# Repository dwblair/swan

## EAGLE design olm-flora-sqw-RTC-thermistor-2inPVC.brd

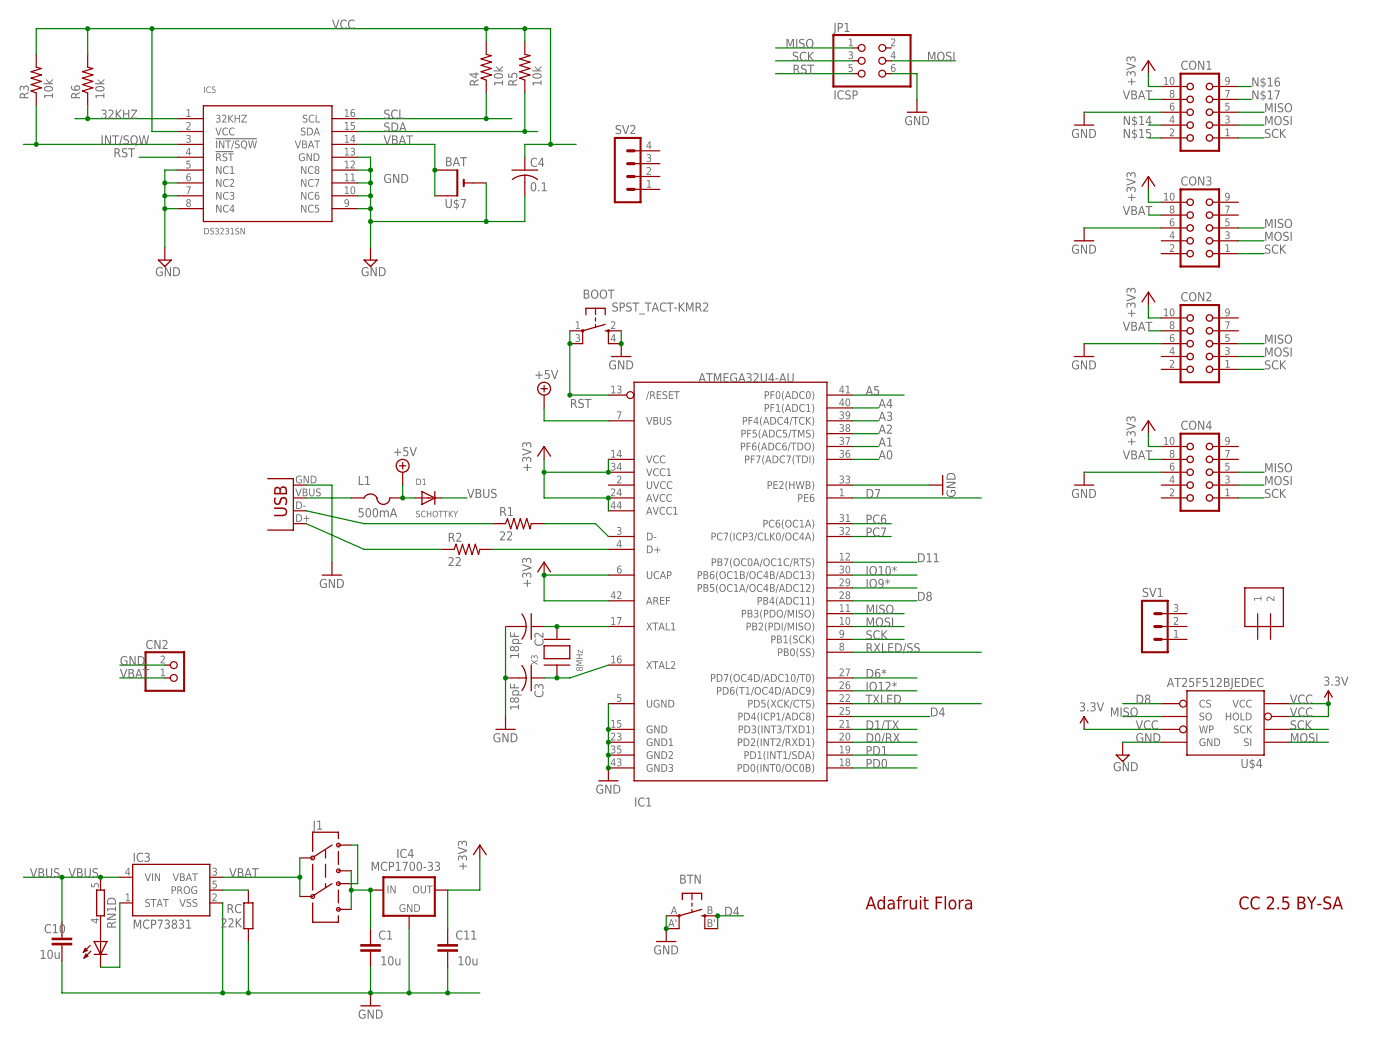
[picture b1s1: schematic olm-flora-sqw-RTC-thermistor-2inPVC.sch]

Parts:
BOOT: SPST_TACT-KMR2; KMR2
BTN: EVQQ2; EVQ-Q2
C1, C10, C11: 10u; C0805
C2, C3: 18pF; C0805K
C4: 0.1; C0805K
CHG: 0805; CHIPLED_0805
CN2: JST_2PIN-SMT-RA; JST-PH-2-SMT-RA
CON1, CON2, CON3, CON4: CON10
D1: SCHOTTKY; SOD-123
IC1: ATMEGA32U4-AU; TQFP44
IC3: MCP73831; SOT23-5
IC4: MCP1700-33; SOT23
IC5: DS3231SN; SO16W
J1: AYZ0202
J2: 1X2-3.5MM
JP1: ICSP; 2X03
L1: 500mA; R1206
R1, R2: 22; R0805
R3, R4, R5, R6: 10k; R0805
RC: 22K; R0805
RN1: 4R-NEXB38V; EXB38V
SV1: MA03-1
SV2: MA04-1
U$4: AT25F512BJEDEC; SO08
U$7: BAT; CR1220-SMD
X1: USBSMD; USB-MINIB
X3: 8MHz; NX5032

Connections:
32KHZ: IC5.1 (32KHZ), R6.1
+3V3: C11.1, CON1.10, CON2.10, CON3.10, CON4.10, IC1.6 (UCAP), IC1.14 (VCC), IC1.24 (AVCC), IC1.34 (VCC1), IC1.42 (AREF), IC1.44 (AVCC1), IC4.2 (OUT)
+5V: D1.A, IC1.7 (VBUS), L1.2
A0: IC1.36 (PF7(ADC7(TDI))
A1: IC1.37 (PF6(ADC6/TDO))
A2: IC1.38 (PF5(ADC5/TMS))
A3: IC1.39 (PF4(ADC4/TCK))
A4: IC1.40 (PF1(ADC1))
A5: IC1.41 (PF0(ADC0))
D0/RX: IC1.20 (PD2(INT2/RXD1))
D1/TX: IC1.21 (PD3(INT3/TXD1))
D4: BTN.B (S), BTN.B' (S1), IC1.25 (PD4(ICP1/ADC8))
D6*: IC1.27 (PD7(OC4D/ADC10/T0))
D7: IC1.1 (PE6)
D8: IC1.28 (PB4(ADC11)), U$4.1_CS (CS)
D11: IC1.12 (PB7(OC0A/OC1C/RTS))
GND: BOOT.2 (S), BOOT.4 (S1), BTN.A, BTN.A' (P1), C1.2, C2.2, C3.2, C4.2, C10.2, C11.2, CN2.2 (1), CON1.6, CON2.6, CON3.6, CON4.6, IC1.5 (UGND), IC1.15 (GND), IC1.23 (GND1), IC1.33 (PE2(HWB)), IC1.35 (GND2), IC1.43 (GND3), IC3.2 (VSS), IC4.1 (GND), IC5.5 (NC1), IC5.6 (NC2), IC5.7 (NC3), IC5.8 (NC4), IC5.9 (NC5), IC5.10 (NC6), IC5.11 (NC7), IC5.12 (NC8), IC5.13 (GND), JP1.6, RC.1, U$4.4_GND (GND), U$7.-, X1.GND
INT/SQW: IC5.3 (!INT/SQW), R3.1
IO9*: IC1.29 (PB5(OC1A/OC4B/ADC12))
IO10*: IC1.30 (PB6(OC1B/OC4B/ADC13))
IO12*: IC1.26 (PD6(T1/OC4D/ADC9))
MISO: CON1.5, CON2.5, CON3.5, CON4.5, IC1.11 (PB3(PDO/MISO)), JP1.1, U$4.2_SO (SO)
MOSI: CON1.3, CON2.3, CON3.3, CON4.3, IC1.10 (PB2(PDI/MISO)), JP1.4, U$4.5_SI (SI)
unnamed: CHG.C, IC3.1 (STAT)
unnamed: R2.1, X1.D+
unnamed: IC1.3 (D-), R1.2
unnamed: IC1.4 (D+), R2.2
unnamed: R1.1, X1.D-
unnamed: C2.1, IC1.17 (XTAL1), X3.P$2
unnamed: C3.1, IC1.16 (XTAL2), X3.P$1
unnamed: IC3.5 (PROG), RC.2
unnamed: J1.3 (1), J1.6 (4)
unnamed: CHG.A, RN1.4 (1)
PC6: IC1.31 (PC6(OC1A))
PC7: IC1.32 (PC7(ICP3/CLK0/OC4A))
PD0: IC1.18 (PD0(INT0/OC0B))
PD1: IC1.19 (PD1(INT1/SDA))
RST: BOOT.1, BOOT.3 (P1), IC1.13 (/RESET), IC5.4 (!RST), JP1.5
RXLED/SS: IC1.8 (PB0(SS))
SCK: CON1.1, CON2.1, CON3.1, CON4.1, IC1.9 (PB1(SCK)), JP1.3, U$4.6_SCK (SCK)
SCL: IC5.16 (SCL), R4.1
SDA: IC5.15 (SDA), R5.1
TXLED: IC1.22 (PD5(XCK/CTS))
VBAT: CN2.1 (2), CON1.8, CON2.8, CON3.8, CON4.8, IC3.3 (VBAT), IC5.14 (VBAT), J1.2, J1.5, U$7.+$1 (+), U$7.+$2 (+1)
VBUS: C10.1, D1.C, IC3.4 (VIN), L1.1, RN1.5 (2), X1.VBUS
VCC: C4.1, IC5.2 (VCC), R3.2, R4.2, R5.2, R6.2, U$4.3_WP (WP), U$4.7_HOLD (HOLD), U$4.8_VCC (VCC)
VDD: C1.1, IC4.3 (IN), J1.1 (3), J1.4 (6)

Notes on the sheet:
Adafruit Flora
CC 2.5 BY-SA

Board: 2 copper layers, 37 parts (1 on the bottom side), 27 nets, no tracks yet.

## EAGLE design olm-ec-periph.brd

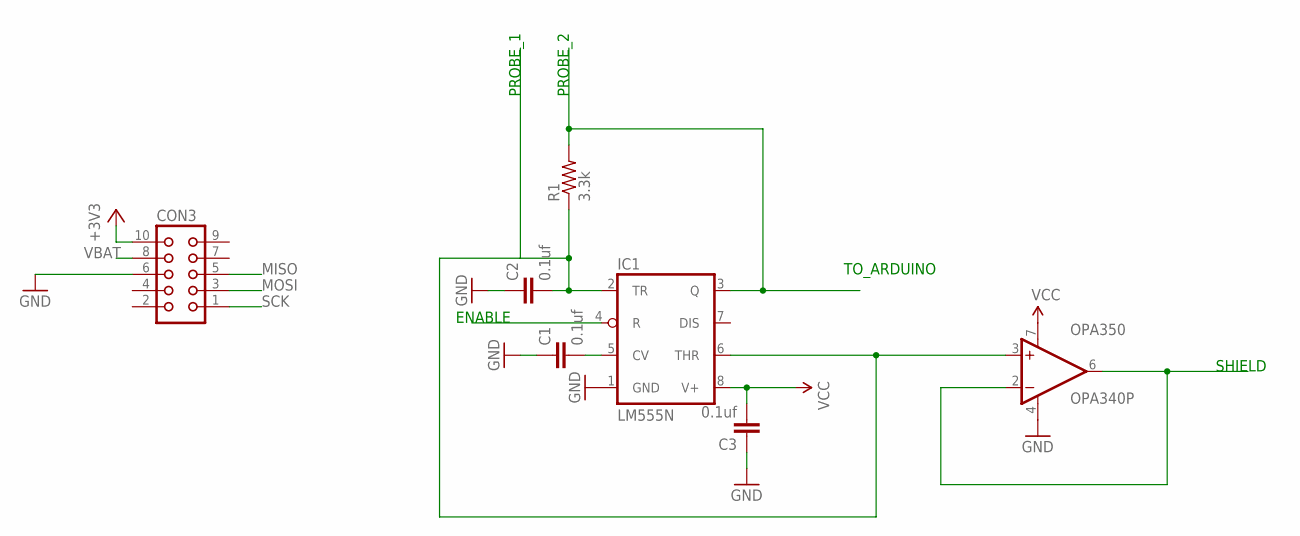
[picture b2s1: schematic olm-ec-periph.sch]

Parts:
C1, C2, C3: 0.1uf; C025-025X050
CON3: CON10
IC1: LM555N; DIL08
OPA350: OPA340P; DIL08
R1: 3.3k; 0207/10

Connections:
+3V3: CON3.10
ENABLE: IC1.4 (R)
GND: C1.1, C2.1, C3.1, CON3.6, IC1.1 (GND), OPA350.4 (V-)
MISO: CON3.5
MOSI: CON3.3
unnamed: C1.2, IC1.5 (CV)
PROBE_1: C2.2, IC1.2 (TR), IC1.6 (THR), OPA350.3 (+IN), R1.1
PROBE_2: IC1.3 (Q), R1.2
SCK: CON3.1
SHIELD: OPA350.2 (-IN), OPA350.6 (OUT)
VBAT: CON3.8
VCC: C3.2, IC1.8 (V+), OPA350.7 (V+)

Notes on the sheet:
PROBE_1
PROBE_2
SHIELD
ENABLE
TO_ARDUINO

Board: 2 copper layers, 7 parts (0 on the bottom side), 6 nets, no tracks yet.

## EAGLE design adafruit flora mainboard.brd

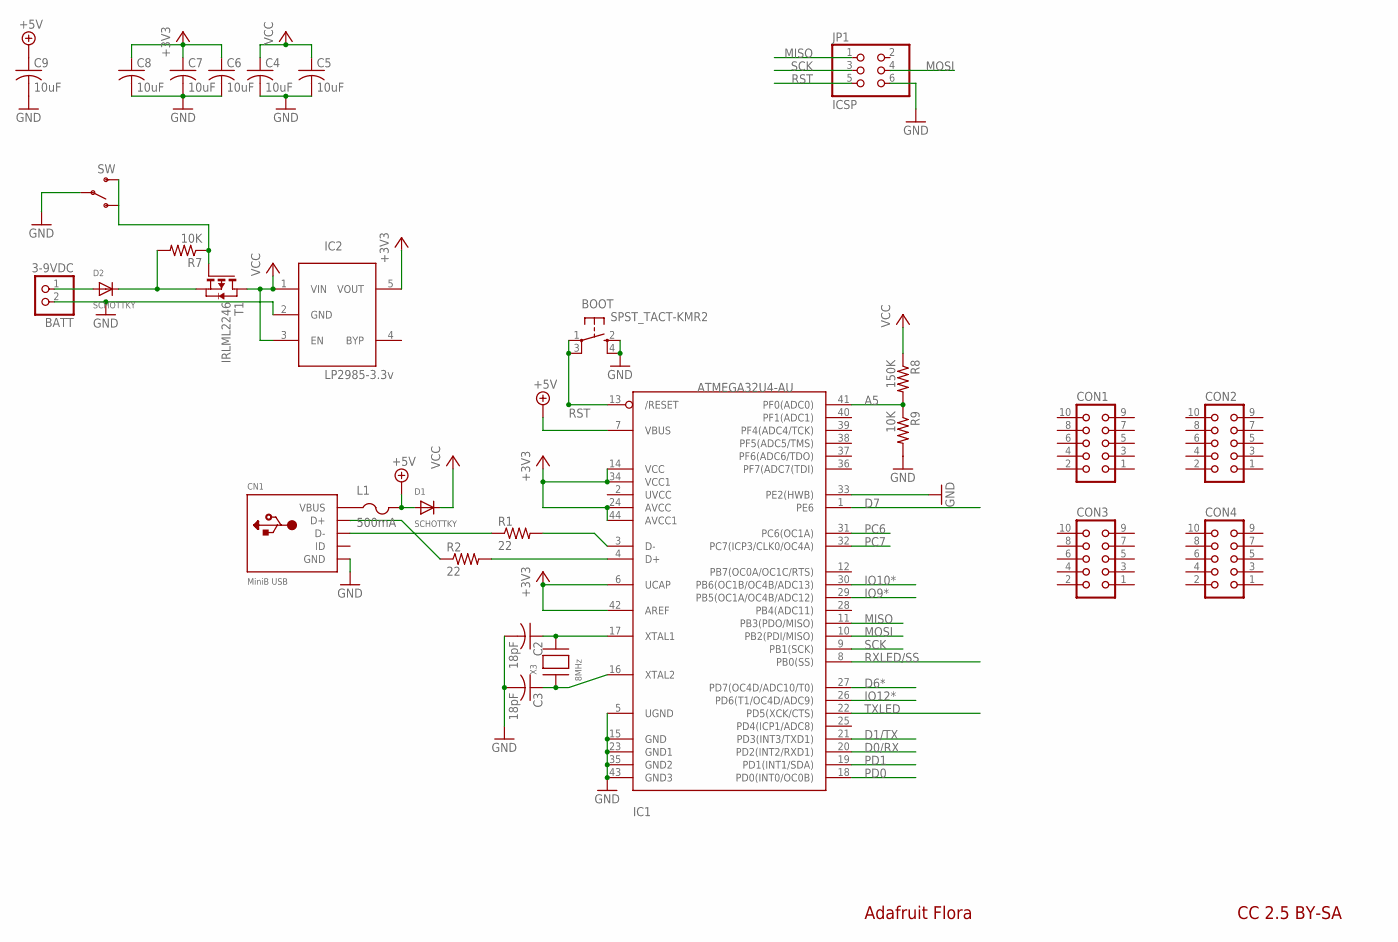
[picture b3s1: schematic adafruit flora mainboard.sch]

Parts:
BATT: 3-9VDC; JST-PH-2-SMT-RA
BOOT: SPST_TACT-KMR2; KMR2
C2, C3: 18pF; C0805K
C4, C5, C6, C7, C8, C9: 10uF; C0805K
CN1: MiniB USB; USB-MINIB_LARGER
CON1, CON2, CON3, CON4: CON10
D1, D2: SCHOTTKY; SOD-123
IC1: ATMEGA32U4-AU; TQFP44
IC2: LP2985-3.3v; SOT23-5L
JP1: ICSP; 2X03
L1: 500mA; R1206
R1, R2: 22; R0805
R7, R9: 10K; R0805
R8: 150K; R0805
SW: SPDT; SWITCH-SPDT-SMD
T1: IRLML2246; SOT-23
X3: 8MHz; NX5032

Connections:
+3V3: C6.1, C7.1, C8.1, IC1.6 (UCAP), IC1.14 (VCC), IC1.24 (AVCC), IC1.34 (VCC1), IC1.42 (AREF), IC1.44 (AVCC1), IC2.5 (VOUT)
+5V: C9.1, D1.A, IC1.7 (VBUS), L1.2
A5: IC1.41 (PF0(ADC0)), R8.2, R9.1
D0/RX: IC1.20 (PD2(INT2/RXD1))
D1/TX: IC1.21 (PD3(INT3/TXD1))
D6*: IC1.27 (PD7(OC4D/ADC10/T0))
D7: IC1.1 (PE6)
GND: BATT.2 (1), BOOT.2 (S), BOOT.4 (S1), C2.2, C3.2, C4.2, C5.2, C6.2, C7.2, C8.2, C9.2, CN1.GND, IC1.5 (UGND), IC1.15 (GND), IC1.23 (GND1), IC1.33 (PE2(HWB)), IC1.35 (GND2), IC1.43 (GND3), IC2.2 (GND), JP1.6, R9.2, SW.2
IO9*: IC1.29 (PB5(OC1A/OC4B/ADC12))
IO10*: IC1.30 (PB6(OC1B/OC4B/ADC13))
IO12*: IC1.26 (PD6(T1/OC4D/ADC9))
MISO: IC1.11 (PB3(PDO/MISO)), JP1.1
MOSI: IC1.10 (PB2(PDI/MISO)), JP1.4
unnamed: CN1.D+, R2.1
unnamed: IC1.3 (D-), R1.2
unnamed: IC1.4 (D+), R2.2
unnamed: CN1.D-, R1.1
unnamed: D2.C, R7.2, T1.2 (S)
unnamed: BATT.1 (2), D2.A
unnamed: C2.1, IC1.17 (XTAL1), X3.P$2
unnamed: C3.1, IC1.16 (XTAL2), X3.P$1
unnamed: R7.1, SW.3 (S), T1.3 (G)
PC6: IC1.31 (PC6(OC1A))
PC7: IC1.32 (PC7(ICP3/CLK0/OC4A))
PD0: IC1.18 (PD0(INT0/OC0B))
PD1: IC1.19 (PD1(INT1/SDA))
RST: BOOT.1, BOOT.3 (P1), IC1.13 (/RESET), JP1.5
RXLED/SS: IC1.8 (PB0(SS))
SCK: IC1.9 (PB1(SCK)), JP1.3
TXLED: IC1.22 (PD5(XCK/CTS))
VBUS: CN1.VBUS, L1.1
VCC: C4.1, C5.1, D1.C, IC2.1 (VIN), IC2.3 (EN), R8.1, T1.1 (D)

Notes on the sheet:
Adafruit Flora
CC 2.5 BY-SA

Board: 2 copper layers, 29 parts (0 on the bottom side), 19 nets, no tracks yet.

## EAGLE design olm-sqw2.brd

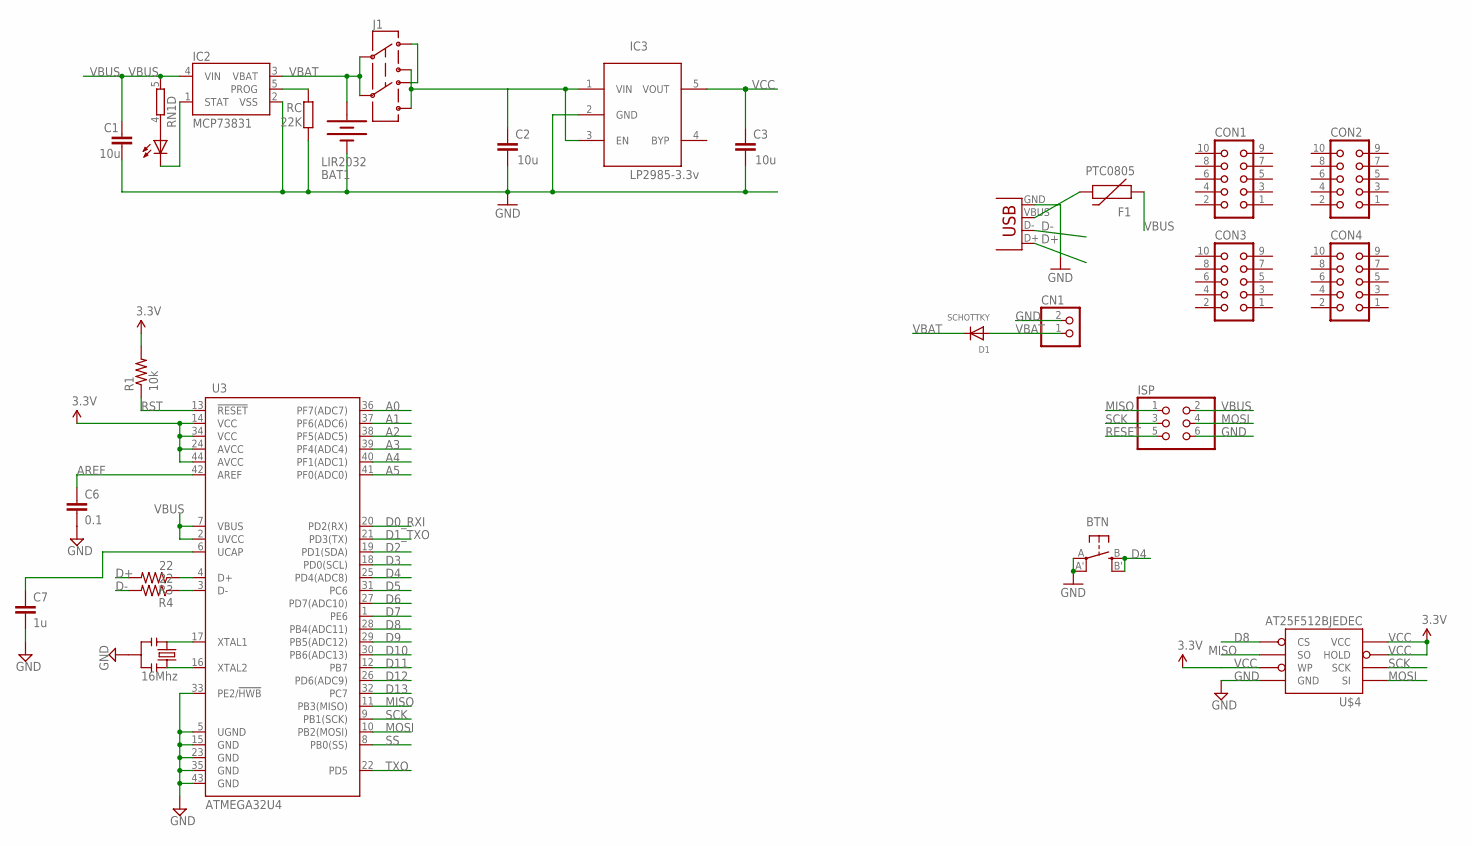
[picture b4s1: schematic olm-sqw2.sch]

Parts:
BAT1: LIR2032; BATTCOM_20MM_PTH_SMT
BTN: EVQQ2; EVQ-Q2
C1, C2, C3: 10u; C0805
C6: 0.1; 0603-CAP
C7: 1u; 0603-CAP
CHG: 0805; CHIPLED_0805
CN1: JST_2PIN-SMT-RA; JST-PH-2-SMT-RA
CON1, CON2, CON3, CON4: CON10
D1: SCHOTTKY; SOD-123
F1: PTC0805; 0805-PTC
IC2: MCP73831; SOT23-5
IC3: LP2985-3.3v; SOT23-5L
ISP: PINHD-2X3; 2X03
J1: AYZ0202
R1: 10k; 0603-RES
R3, R4: 22; 0603-RES
RC: 22K; R0805
RN1: 4R-NEXB38V; EXB38V
U3: ATMEGA32U4; QFN-44-NOPAD
U$4: AT25F512BJEDEC; SO08
X1: USBSMD; USB-MINIB
X2: 16Mhz; RESONATOR-SMD

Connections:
A0: U3.36 (PF7(ADC7))
A1: U3.37 (PF6(ADC6))
A2: U3.38 (PF5(ADC5))
A3: U3.39 (PF4(ADC4))
A4: U3.40 (PF1(ADC1))
A5: U3.41 (PF0(ADC0))
AREF: C6.1, U3.42 (AREF)
D0_RXI: U3.20 (PD2(RX))
D1_TXO: U3.21 (PD3(TX))
D2: U3.19 (PD1(SDA))
D3: U3.18 (PD0(SCL))
D4: BTN.B (S), BTN.B' (S1), U3.25 (PD4(ADC8))
D5: U3.31 (PC6)
D6: U3.27 (PD7(ADC10))
D7: U3.1 (PE6)
D8: U3.28 (PB4(ADC11)), U$4.1_CS (CS)
D9: U3.29 (PB5(ADC12))
D10: U3.30 (PB6(ADC13))
D11: U3.12 (PB7)
D12: U3.26 (PD6(ADC9))
D13: U3.32 (PC7)
D+: R3.2, X1.D+
D-: R4.2, X1.D-
GND: BAT1.P$1 (-), BTN.A, BTN.A' (P1), C1.2, C2.2, C3.2, C6.2, C7.2, CN1.2 (1), IC2.2 (VSS), IC3.2 (GND), ISP.6, RC.1, U3.5 (UGND), U3.15 (GND), U3.23 (GND), U3.33 (PE2/!HWB), U3.35 (GND), U3.43 (GND), U$4.4_GND (GND), X1.GND, X2.2
MISO: ISP.1, U3.11 (PB3(MISO)), U$4.2_SO (SO)
MOSI: ISP.4, U3.10 (PB2(MOSI)), U$4.5_SI (SI)
unnamed: J1.3 (1), J1.6 (4)
unnamed: U3.16 (XTAL2), X2.3
unnamed: CHG.C, IC2.1 (STAT)
unnamed: IC2.5 (PROG), RC.2
unnamed: U3.17 (XTAL1), X2.1
unnamed: C7.1, U3.6 (UCAP)
unnamed: R3.1, U3.4 (D+)
unnamed: CHG.A, RN1.4 (1)
unnamed: R4.1, U3.3 (D-)
RESET: ISP.5
RST: R1.1, U3.13 (!RESET)
SCK: ISP.3, U3.9 (PB1(SCK)), U$4.6_SCK (SCK)
SS: U3.8 (PB0(SS))
TXO: U3.22 (PD5)
VBAT: BAT1.P$2 (+), CN1.1 (2), D1.A, D1.C, IC2.3 (VBAT), J1.2, J1.5
VBUS: C1.1, F1.1, F1.2, IC2.4 (VIN), ISP.2, RN1.5 (2), U3.2 (UVCC), U3.7 (VBUS), X1.VBUS
VCC: C3.1, IC3.5 (VOUT), R1.2, U3.14 (VCC), U3.24 (AVCC), U3.34 (VCC), U3.44 (AVCC), U$4.3_WP (WP), U$4.7_HOLD (HOLD), U$4.8_VCC (VCC)
VDD: C2.1, IC3.1 (VIN), IC3.3 (EN), J1.1 (3), J1.4 (6)

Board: 2 copper layers, 28 parts (1 on the bottom side), 23 nets, no tracks yet.

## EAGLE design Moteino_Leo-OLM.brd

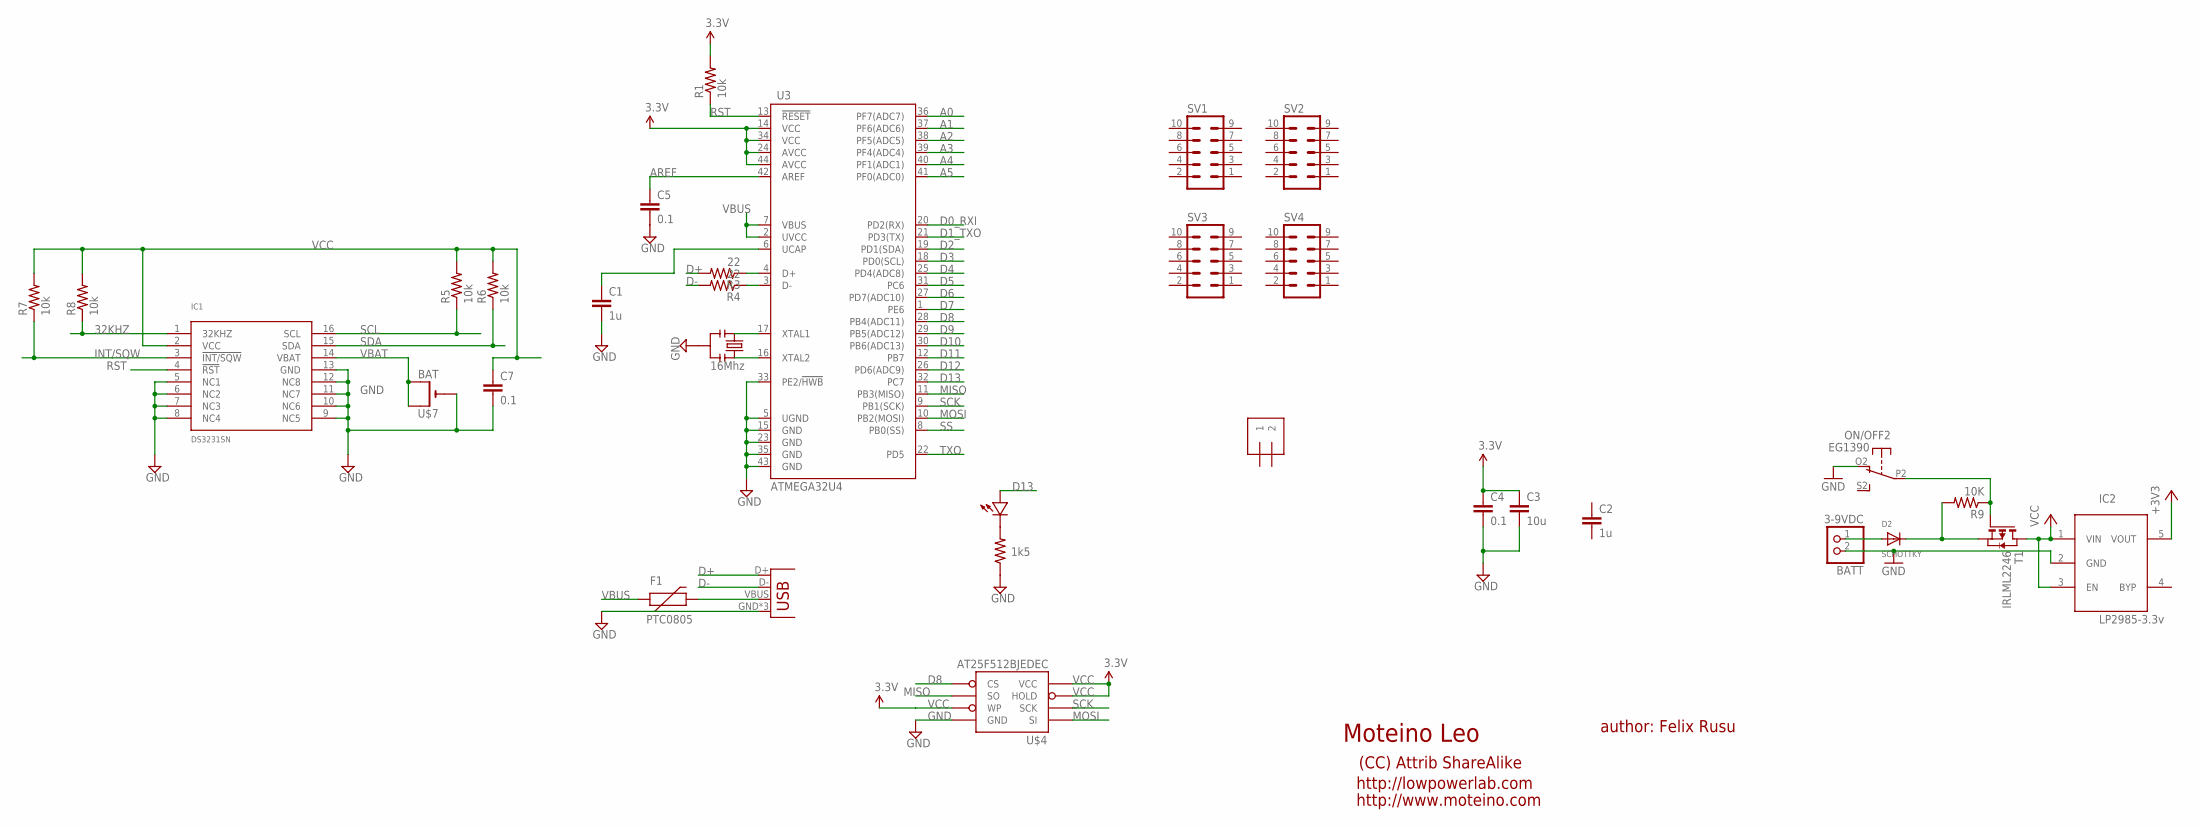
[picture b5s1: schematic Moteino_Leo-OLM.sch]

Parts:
BATT: 3-9VDC; JST-PH-2-SMT-RA
C1, C2: 1u; 0603-CAP
C3: 10u; 0805-CAP
C4, C5, C7: 0.1; 0603-CAP
D2: SCHOTTKY; SOD-123
F1: PTC0805; 0805-PTC
IC1: DS3231SN; SO16W
IC2: LP2985-3.3v; SOT23-5L
J1: 1X2-3.5MM
JP3: USB-MICROB
ON/OFF: EG1390
R1, R5, R6, R7, R8: 10k; 0603-RES
R2: 1k5; 0603-RES
R3, R4: 22; 0603-RES
R9: 10K; R0805
SV1, SV2, SV3, SV4: MA05-2
T1: IRLML2246; SOT-23
U3: ATMEGA32U4; QFN-44-NOPAD
U$2: LED0603; 0603-LED
U$4: AT25F512BJEDEC; SO08
U$7: BAT; CR1220-SMD
X1: 16Mhz; RESONATOR-SMD

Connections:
32KHZ: IC1.1 (32KHZ), R8.1
+3V3: IC2.5 (VOUT)
A0: U3.36 (PF7(ADC7))
A1: U3.37 (PF6(ADC6))
A2: U3.38 (PF5(ADC5))
A3: U3.39 (PF4(ADC4))
A4: U3.40 (PF1(ADC1))
A5: U3.41 (PF0(ADC0))
AREF: C5.1, U3.42 (AREF)
D0_RXI: U3.20 (PD2(RX))
D1_TXO: U3.21 (PD3(TX))
D2: U3.19 (PD1(SDA))
D3: U3.18 (PD0(SCL))
D4: U3.25 (PD4(ADC8))
D5: U3.31 (PC6)
D6: U3.27 (PD7(ADC10))
D7: U3.1 (PE6)
D8: U3.28 (PB4(ADC11)), U$4.1_CS (CS)
D9: U3.29 (PB5(ADC12))
D10: U3.30 (PB6(ADC13))
D11: U3.12 (PB7)
D12: U3.26 (PD6(ADC9))
D13: U3.32 (PC7), U$2.PLUS
D+: JP3.D+, R3.2
D-: JP3.D-, R4.2
GND: BATT.2 (1), C1.2, C3.2, C4.2, C5.2, C7.2, IC1.5 (NC1), IC1.6 (NC2), IC1.7 (NC3), IC1.8 (NC4), IC1.9 (NC5), IC1.10 (NC6), IC1.11 (NC7), IC1.12 (NC8), IC1.13 (GND), IC2.2 (GND), JP3.GND, JP3.MT1 (GND), JP3.MT2 (GND), ON/OFF.O2 (O), R2.1, U3.5 (UGND), U3.15 (GND), U3.23 (GND), U3.33 (PE2/!HWB), U3.35 (GND), U3.43 (GND), U$4.4_GND (GND), U$7.-, X1.2
INT/SQW: IC1.3 (!INT/SQW), R7.1
MISO: U3.11 (PB3(MISO)), U$4.2_SO (SO)
MOSI: U3.10 (PB2(MOSI)), U$4.5_SI (SI)
unnamed: R2.2, U$2.MINUS
unnamed: BATT.1 (2), D2.A
unnamed: D2.C, R9.2, T1.2 (S)
unnamed: U3.16 (XTAL2), X1.3
unnamed: U3.17 (XTAL1), X1.1
unnamed: C1.1, U3.6 (UCAP)
unnamed: R3.1, U3.4 (D+)
unnamed: R4.1, U3.3 (D-)
unnamed: ON/OFF.P2, R9.1, T1.3 (G)
RST: IC1.4 (!RST), R1.1, U3.13 (!RESET)
SCK: U3.9 (PB1(SCK)), U$4.6_SCK (SCK)
SCL: IC1.16 (SCL), R5.1
SDA: IC1.15 (SDA), R6.1
SS: U3.8 (PB0(SS))
TXO: U3.22 (PD5)
USBPOWER: F1.2, JP3.VBUS
VBAT: IC1.14 (VBAT), U$7.+$1 (+), U$7.+$2 (+1)
VBUS: F1.1, U3.2 (UVCC), U3.7 (VBUS)
VCC: C3.1, C4.1, C7.1, IC1.2 (VCC), IC2.1 (VIN), IC2.3 (EN), R1.2, R5.2, R6.2, R7.2, R8.2, T1.1 (D), U3.14 (VCC), U3.24 (AVCC), U3.34 (VCC), U3.44 (AVCC), U$4.3_WP (WP), U$4.7_HOLD (HOLD), U$4.8_VCC (VCC)

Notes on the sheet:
Moteino Leo
author: Felix Rusu
http://lowpowerlab.com
(CC) Attrib ShareAlike
http://www.moteino.com

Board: 2 copper layers, 33 parts (4 on the bottom side), 27 nets, no tracks yet.

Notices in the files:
parts and their libraries:
SparkFun-Connectors: Licensing: CC v3.0 Share-Alike You are welcome to use this library for commercial purposes.
microbuilder: This work is placed in the public domain, and may be freely used for commercial and non-commercial work with the following conditions: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
